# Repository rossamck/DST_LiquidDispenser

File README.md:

# GUSTAVO - Liquid Dispensing Client

This repo hosts the software and schematics for the GUSTAVO project.

## Installation
### Building from Source

1. Clone this repository:

```bash
git clone https://github.com/rossamck/DST_LiquidDispenser.git
```

2. Navigate to the project directory:
```bash
cd DST_LiquidDispenser
```

3. Install dependencies: 
```bash
npm install
```

4. Run the application:
```bash
npm start
```

### Running release application
1. Download the appropriate installation file for your operating system from the [Releases](https://github.com/rossamck/DST_LiquidDispenser/releases) page.

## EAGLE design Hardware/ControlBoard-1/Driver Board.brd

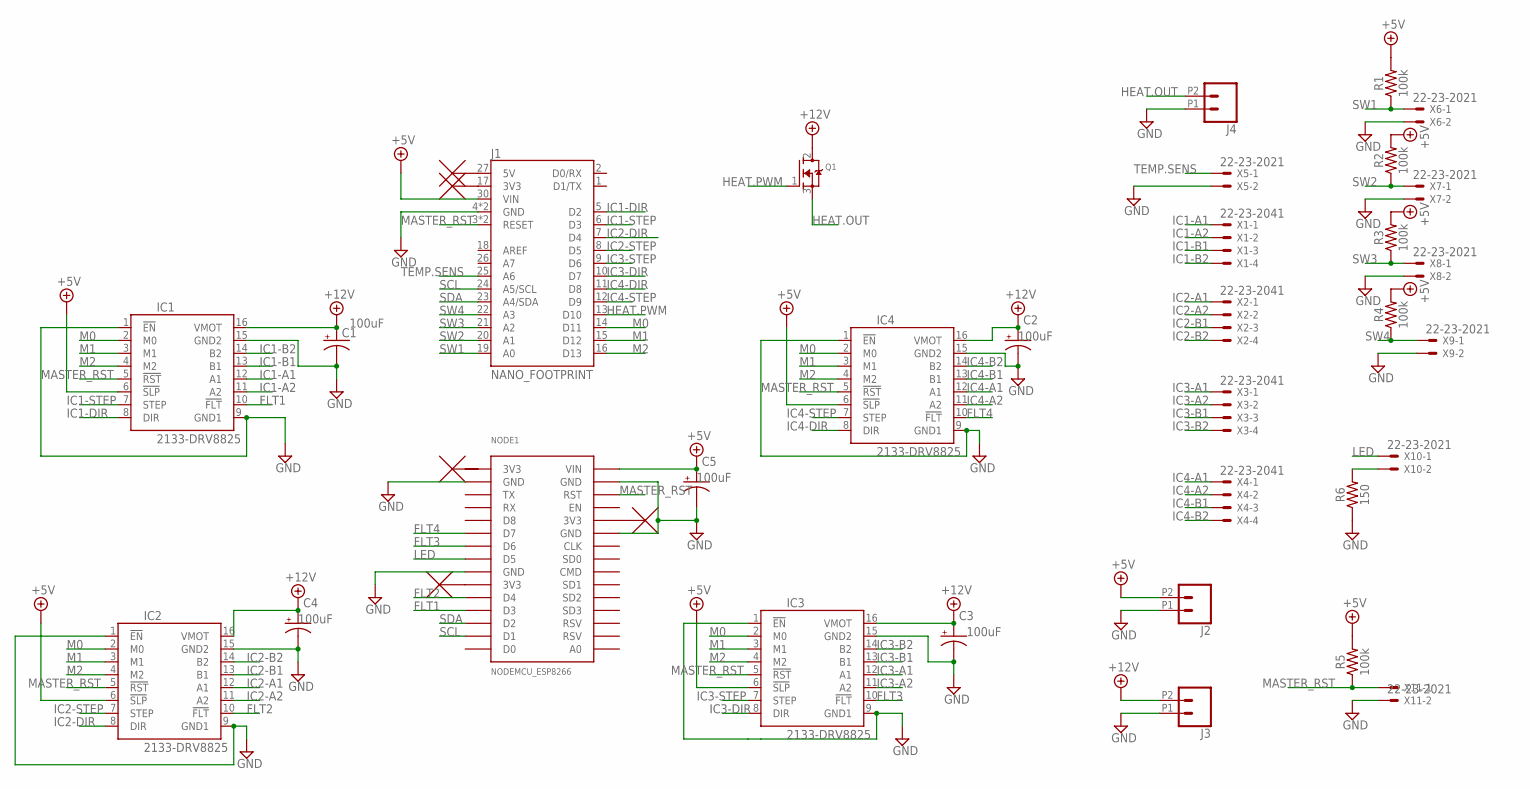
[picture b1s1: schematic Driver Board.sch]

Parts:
C1, C2, C3, C4, C5: CPOL-USD; PANASONIC_D
IC1, IC2, IC3, IC4: 2133-DRV8825; DRV8825
J1: NANO_FOOTPRINT; NANO
J2, J3, J4: CONN_02SCREWTERMINAL-6.35MM-2; 1X02_6.35_SCREWTERM
NODE1: NODEMCU_ESP8266
Q1: MOSFET-NGDS_TO220V; TO220V
R1, R2, R3, R4, R5: 100k; 0805
R6: 150; 0805
X1, X2, X3, X4: 22-23-2041
X5, X6, X7, X8, X9, X10, X11: 22-23-2021

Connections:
3V3: NODE1.3V3@1 (3V3)
+5V: C5.+, IC1.6 (!SLP), IC2.6 (!SLP), IC3.6 (!SLP), IC4.6 (!SLP), J1.30 (VIN), J2.P2 (1), NODE1.VIN, R1.2, R2.2, R3.2, R4.2, R5.2
+12V: C1.+, C2.+, C3.+, C4.+, IC1.16 (VMOT), IC2.16 (VMOT), IC3.16 (VMOT), IC4.16 (VMOT), J3.P2 (1), Q1.2 (D)
FLT1: IC1.10 (!FLT), NODE1.D3
FLT2: IC2.10 (!FLT), NODE1.D4
FLT3: IC3.10 (!FLT), NODE1.D6
FLT4: IC4.10 (!FLT), NODE1.D7
GND: C1.-, C2.-, C3.-, C4.-, C5.-, IC1.1 (!EN), IC1.9 (GND1), IC1.15 (GND2), IC2.1 (!EN), IC2.9 (GND1), IC2.15 (GND2), IC3.1 (!EN), IC3.9 (GND1), IC3.15 (GND2), IC4.1 (!EN), IC4.9 (GND1), IC4.15 (GND2), J1.4 (GND), J1.29 (GND), J2.P1 (2), J3.P1 (2), J4.P1 (2), NODE1.GND@1 (GND), NODE1.GND@2 (GND), NODE1.GND@3 (GND), NODE1.GND@4 (GND), R6.1, X5.2, X6.2, X7.2, X8.2, X9.2, X11.2
HEAT.OUT: J4.P2 (1), Q1.3 (S)
HEAT.PWM: J1.13 (D10), Q1.1 (G)
IC1-A1: IC1.12 (A1), X1.1
IC1-A2: IC1.11 (A2), X1.2
IC1-B1: IC1.13 (B1), X1.3
IC1-B2: IC1.14 (B2), X1.4
IC1-DIR: IC1.8 (DIR), J1.5 (D2)
IC1-STEP: IC1.7 (STEP), J1.6 (D3)
IC2-A1: IC2.12 (A1), X2.1
IC2-A2: IC2.11 (A2), X2.2
IC2-B1: IC2.13 (B1), X2.3
IC2-B2: IC2.14 (B2), X2.4
IC2-DIR: IC2.8 (DIR), J1.7 (D4)
IC2-STEP: IC2.7 (STEP), J1.8 (D5)
IC3-A1: IC3.12 (A1), X3.1
IC3-A2: IC3.11 (A2), X3.2
IC3-B1: IC3.13 (B1), X3.3
IC3-B2: IC3.14 (B2), X3.4
IC3-DIR: IC3.8 (DIR), J1.10 (D7)
IC3-STEP: IC3.7 (STEP), J1.9 (D6)
IC4-A1: IC4.12 (A1), X4.1
IC4-A2: IC4.11 (A2), X4.2
IC4-B1: IC4.13 (B1), X4.3
IC4-B2: IC4.14 (B2), X4.4
IC4-DIR: IC4.8 (DIR), J1.11 (D8)
IC4-STEP: IC4.7 (STEP), J1.12 (D9)
LED: NODE1.D5, X10.1
M0: IC1.2 (M0), IC2.2 (M0), IC3.2 (M0), IC4.2 (M0), J1.14 (D11)
M1: IC1.3 (M1), IC2.3 (M1), IC3.3 (M1), IC4.3 (M1), J1.15 (D12)
M2: IC1.4 (M2), IC2.4 (M2), IC3.4 (M2), IC4.4 (M2), J1.16 (D13)
MASTER_RST: IC1.5 (!RST), IC2.5 (!RST), IC3.5 (!RST), IC4.5 (!RST), J1.3 (RESET), J1.28 (RESET), NODE1.RST, R5.1, X11.1
unnamed: R6.2, X10.2
SCL: J1.24 (A5/SCL), NODE1.D1
SDA: J1.23 (A4/SDA), NODE1.D2
SW1: J1.19 (A0), R1.1, X6.1
SW2: J1.20 (A1), R2.1, X7.1
SW3: J1.21 (A2), R3.1, X8.1
SW4: J1.22 (A3), R4.1, X9.1
TEMP.SENS: J1.25 (A6), X5.1

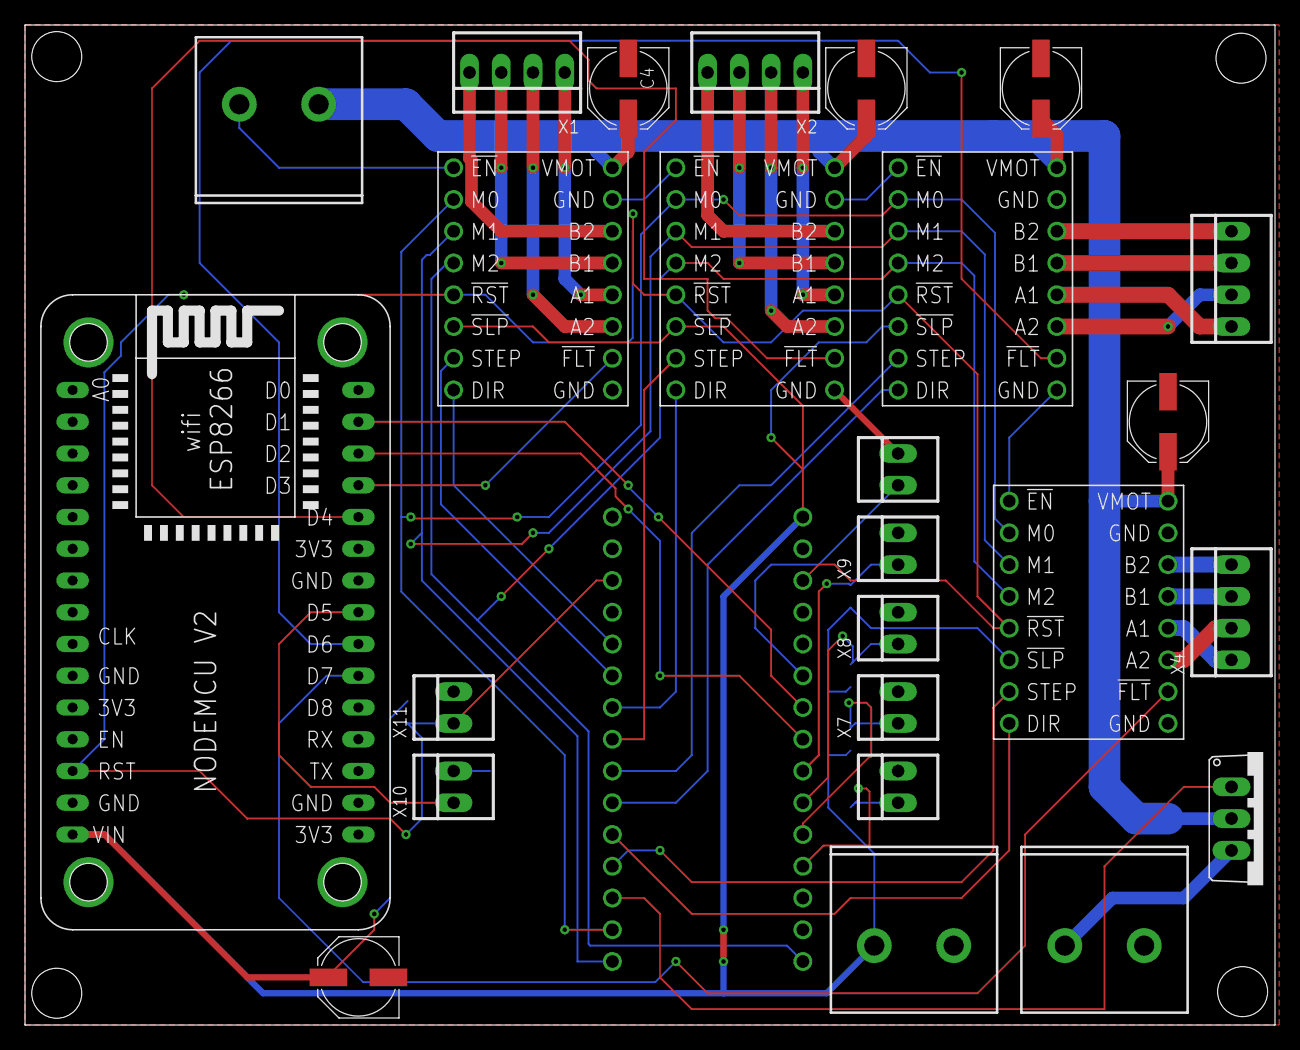
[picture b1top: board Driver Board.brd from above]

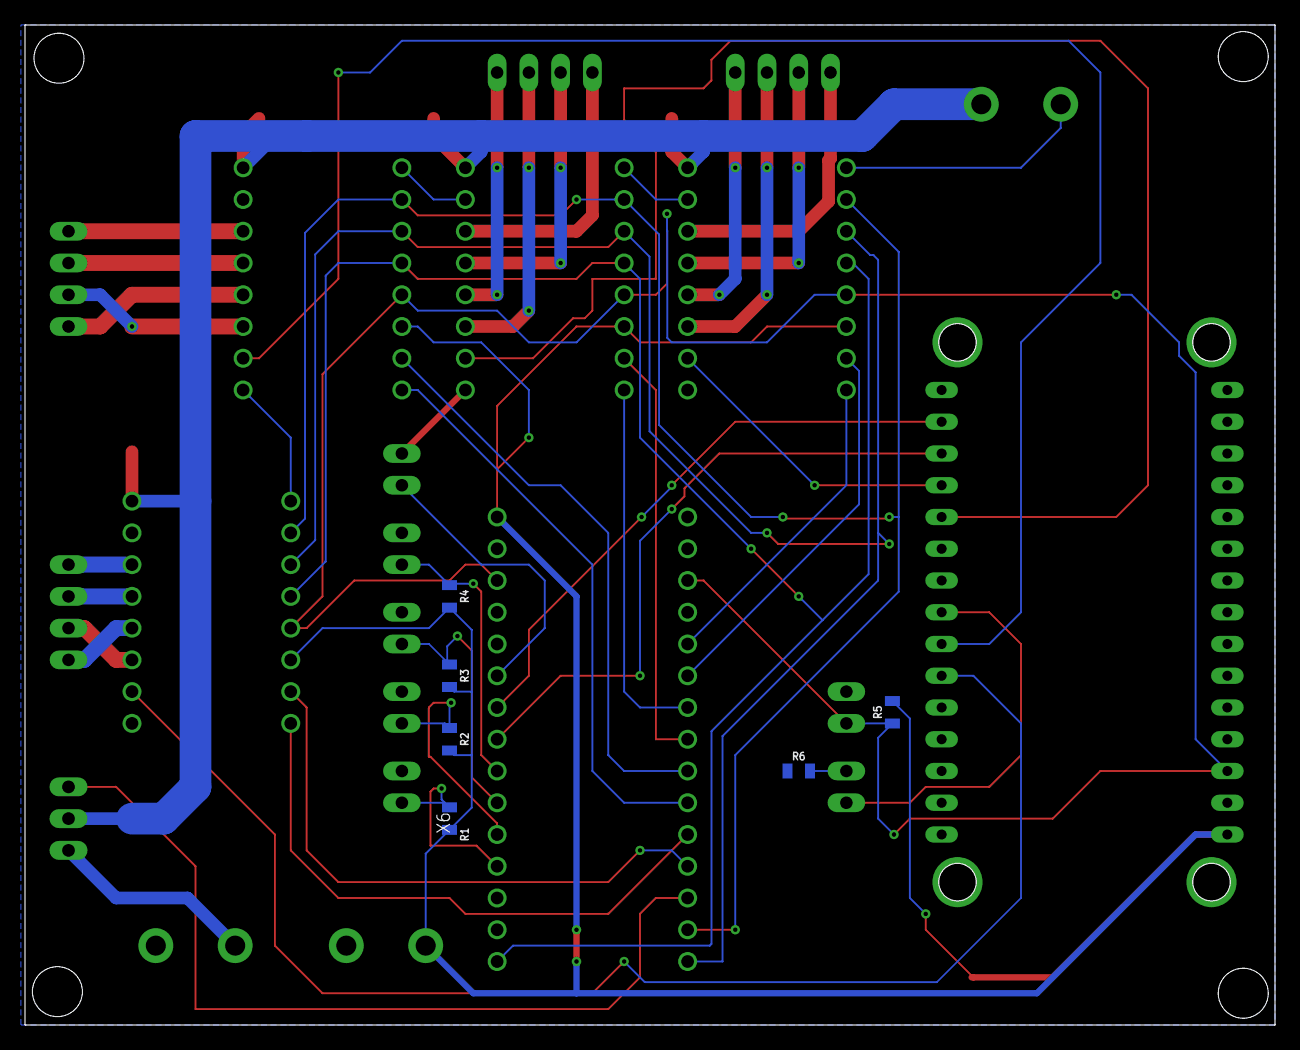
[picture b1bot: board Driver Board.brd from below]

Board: 2 copper layers, 100.0 x 80.0 mm, 32 parts (6 on the bottom side), 46 nets.

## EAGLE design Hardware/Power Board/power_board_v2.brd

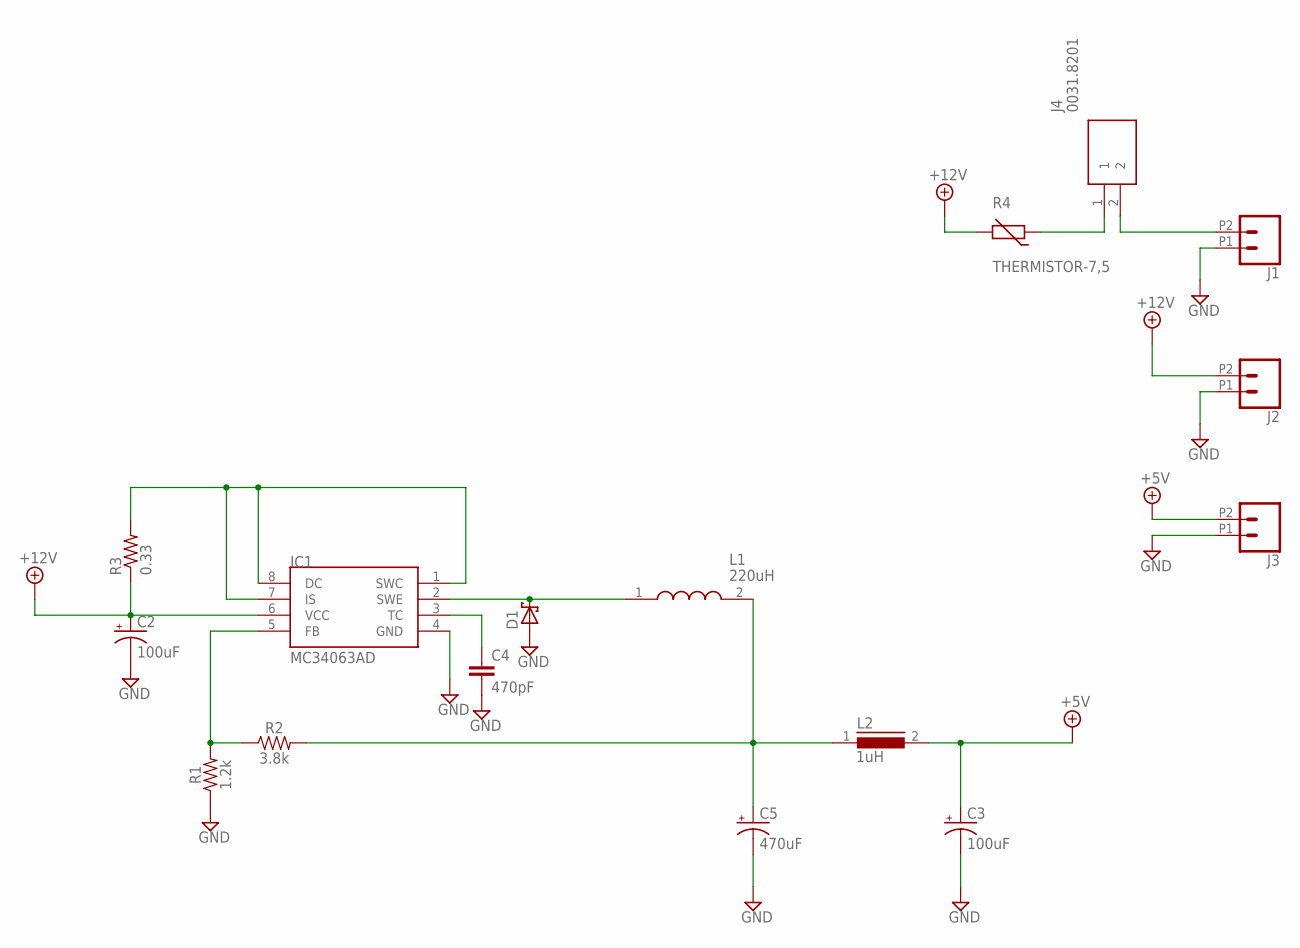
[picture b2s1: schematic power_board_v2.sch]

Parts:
C2, C3: 100uF; PANASONIC_D
C4: 470pF; C0805
C5: 470uF; PANASONIC_F
D1: SCHOTTKY-DIODEDO41; DO41-10
IC1: MC34063AD; SOIC8
J1, J2, J3: CONN_02SCREWTERMINAL-6.35MM-2; 1X02_6.35_SCREWTERM
J4: 0031.8201
L1: 220uH; WE-TI_809589
L2: 1uH; MICC12
R1: 1.2k; 0805
R2: 3.8k; 0805
R3: 0.33; R2512
R4: THERMISTOR-7,5; R-7,5

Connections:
+5V: C3.+, J3.P2 (1), L2.2
+12V: C2.+, IC1.6 (VCC), J2.P2 (1), R3.1, R4.2
GND: C2.-, C3.-, C4.2, C5.-, D1.A, IC1.4 (GND), J1.P1 (2), J2.P1 (2), J3.P1 (2), R1.1
unnamed: D1.C, IC1.2 (SWE), L1.1
unnamed: C5.+, L1.2, L2.1, R2.2
unnamed: IC1.1 (SWC), IC1.7 (IS), IC1.8 (DC), R3.2
unnamed: C4.1, IC1.3 (TC)
unnamed: IC1.5 (FB), R1.2, R2.1
unnamed: J1.P2 (1), J4.2
unnamed: J4.1, R4.1

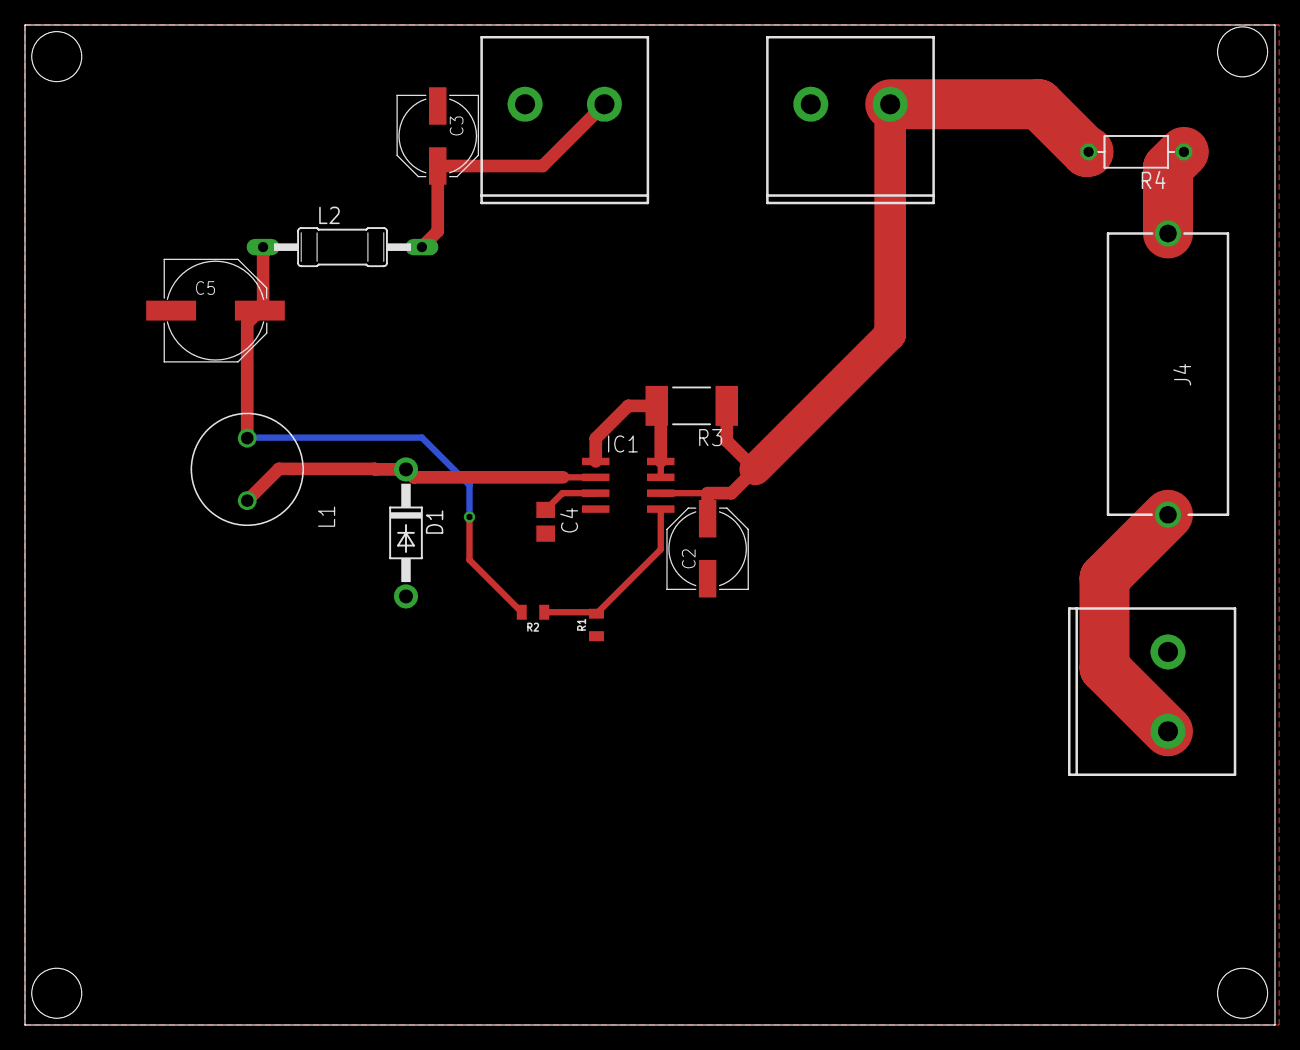
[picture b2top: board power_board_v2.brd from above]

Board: 2 copper layers, 100.0 x 80.0 mm, 16 parts (0 on the bottom side), 10 nets.

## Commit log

2023-03-13 added initial files
2023-03-26 added temp html tests
2023-03-26 added motor testing code
2023-03-28 updated html to use highlight and select
2023-03-29 bootstrap test
2023-04-04 test compile
2023-04-09 updated html structure
2023-04-09 Initialize project using Create React App
2023-04-10 updated layout
2023-04-11 updated websocket functions
2023-04-11 temp commit
2023-04-11 removed old files from main branch
2023-04-11 temp readme update test
2023-04-11 added preset functionality
2023-04-12 added ability to track currently dispensing well
2023-04-12 fixed bug with clear all
2023-04-12 update config
2023-04-12 updated auto compile
2023-04-12 new update
2023-04-12 new test 2
2023-04-12 new test 3
2023-04-12 added auto-start sh script
2023-04-12 temp test commit
2023-04-12 test 4
2023-04-12 Update build.yml 2
2023-04-12 updated action test
2023-04-12 test action update
2023-04-12 updated temp esp IP
2023-04-12 updated burger menu animation
2023-04-13 updated info panel layout
2023-04-14 fixed preset selector
2023-04-14 updated sidebar element
2023-05-01 temp update
2023-05-05 added ability to handle multiple liquid sources
2023-05-05 added liquidsource module
2023-05-06 added manual movement adjustment buttons
2023-05-07 added new counter
2023-05-07 added manual movement controls and linked to esp
2023-05-07 added ability to change IP of esp
2023-05-08 updated arduino test files
2023-05-08 updated motor control code
2023-05-08 added tabs for movementcontrol
2023-05-09 updated arduino code
2023-05-10 temp
2023-05-10 temp update broken z and pip control
2023-05-10 fixed z axis bug
2023-05-10 new movement stuff
2023-05-10 updated movetolimit
2023-05-10 huge refactoring of i2c communication code
2023-05-10 added coordinates to statusindicator
2023-05-11 updated coordinates system
2023-05-12 added positional layout
2023-05-12 linked well selection to coordinate movement
2023-05-13 updated coord message to send when dispensing well
2023-05-13 added electron builder config
2023-05-13 updated well spacing
2023-05-13 bug fixes
2023-05-13 temp update, broken, use last commit in the meantime
2023-05-14 updated absolute coordinate positinos
2023-05-14 added job queue layout
2023-05-15 auto updates
2023-05-15 Update build.yml again
2023-05-15 Update build.yml test
2023-05-15 updated package.json to fix bug
2023-05-15 reverted to previous build.yml
2023-05-15 updated package.json again
2023-05-15 package.json updated once again
2023-05-15 added windows build workflow
2023-05-15 test windows build
2023-05-15 updated windows workflow
2023-05-15 fixed typo in package.json
2023-05-15 attempt 2
2023-05-15 temp2
2023-05-15 new electron.js attempt 1
2023-05-15 new electron.js attempt 2
2023-05-15 new electron.js attempt 3
2023-05-15 new electron.js attempt 5
2023-05-15 new electron.js attempt 6
2023-05-15 updated mac action
2023-05-15 updated mac action 2
2023-05-15 temp test
2023-05-15 added missing code
2023-05-15 coordinate calibration
2023-05-15 fixed preset bug
2023-05-16 test1
2023-05-16 added multiple well plate options in json format
2023-05-16 first release test
2023-05-16 updated a lot of stuff
2023-05-16 test
2023-05-16 pre lab test
2023-05-16 added sourcecolours
2023-05-17 post lab test temp working demo
2023-05-17 post demo
2023-05-20 updated message system
2023-05-20 simplified job tracking
2023-05-20 testing workflow
2023-05-20 testing multiple os
2023-05-20 fixed yml typo
2023-05-20 moved electron.js
2023-05-20 copyfiles test
2023-05-20 another test
2023-05-20 another test2
2023-05-20 another test3
2023-05-20 another test4
2023-05-20 test2
2023-05-20 updated node in yml
2023-05-20 test3
2023-05-20 added token
2023-05-20 electron no publish test
2023-05-20 server test
2023-05-20 server test corrected port
2023-05-20 updated ssh stuff
2023-05-20 temporarily removed arm mac
2023-05-20 fixed auto update
2023-05-21 auto publish test
2023-05-21 auto publish test token check
2023-05-21 auto publish test token check3
2023-05-21 auto publish test token check4
2023-05-21 auto publish test token check5
2023-05-21 auto publish test token check6
2023-05-21 auto publish test token check7
2023-05-21 auto publish test token check8
2023-05-21 auto publish test token check9
2023-05-21 auto publish test token check10
2023-05-21 auto publish test token check11
2023-05-21 auto publish test token check12
2023-05-21 auto publish new test 1
2023-05-21 auto publish new test 1.1
2023-05-21 auto publish new test 2
2023-05-21 added auto update on version change
2023-05-21 fixed branch bug
2023-05-21 switched mac update to include zip
2023-05-21 zip attempt 2
2023-05-21 zip only attempt
2023-05-21 fixed naming mistake
2023-05-21 fixed naming mistake properly this time
2023-05-22 various QOL improvements
2023-05-22 updated json location
2023-05-22 added ability to edit json directly in app
2023-05-24 BETA: new JSON editor and loading animation
2023-05-28 disabled devtools when disconnected and updated modal design
2023-05-28 updated readme and added hardware

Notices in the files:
parts and their libraries:
SparkFun-Boards: Licensing: Creative Commons ShareAlike 4.0 International - https://creativecommons.org/licenses/by-sa/4.0
